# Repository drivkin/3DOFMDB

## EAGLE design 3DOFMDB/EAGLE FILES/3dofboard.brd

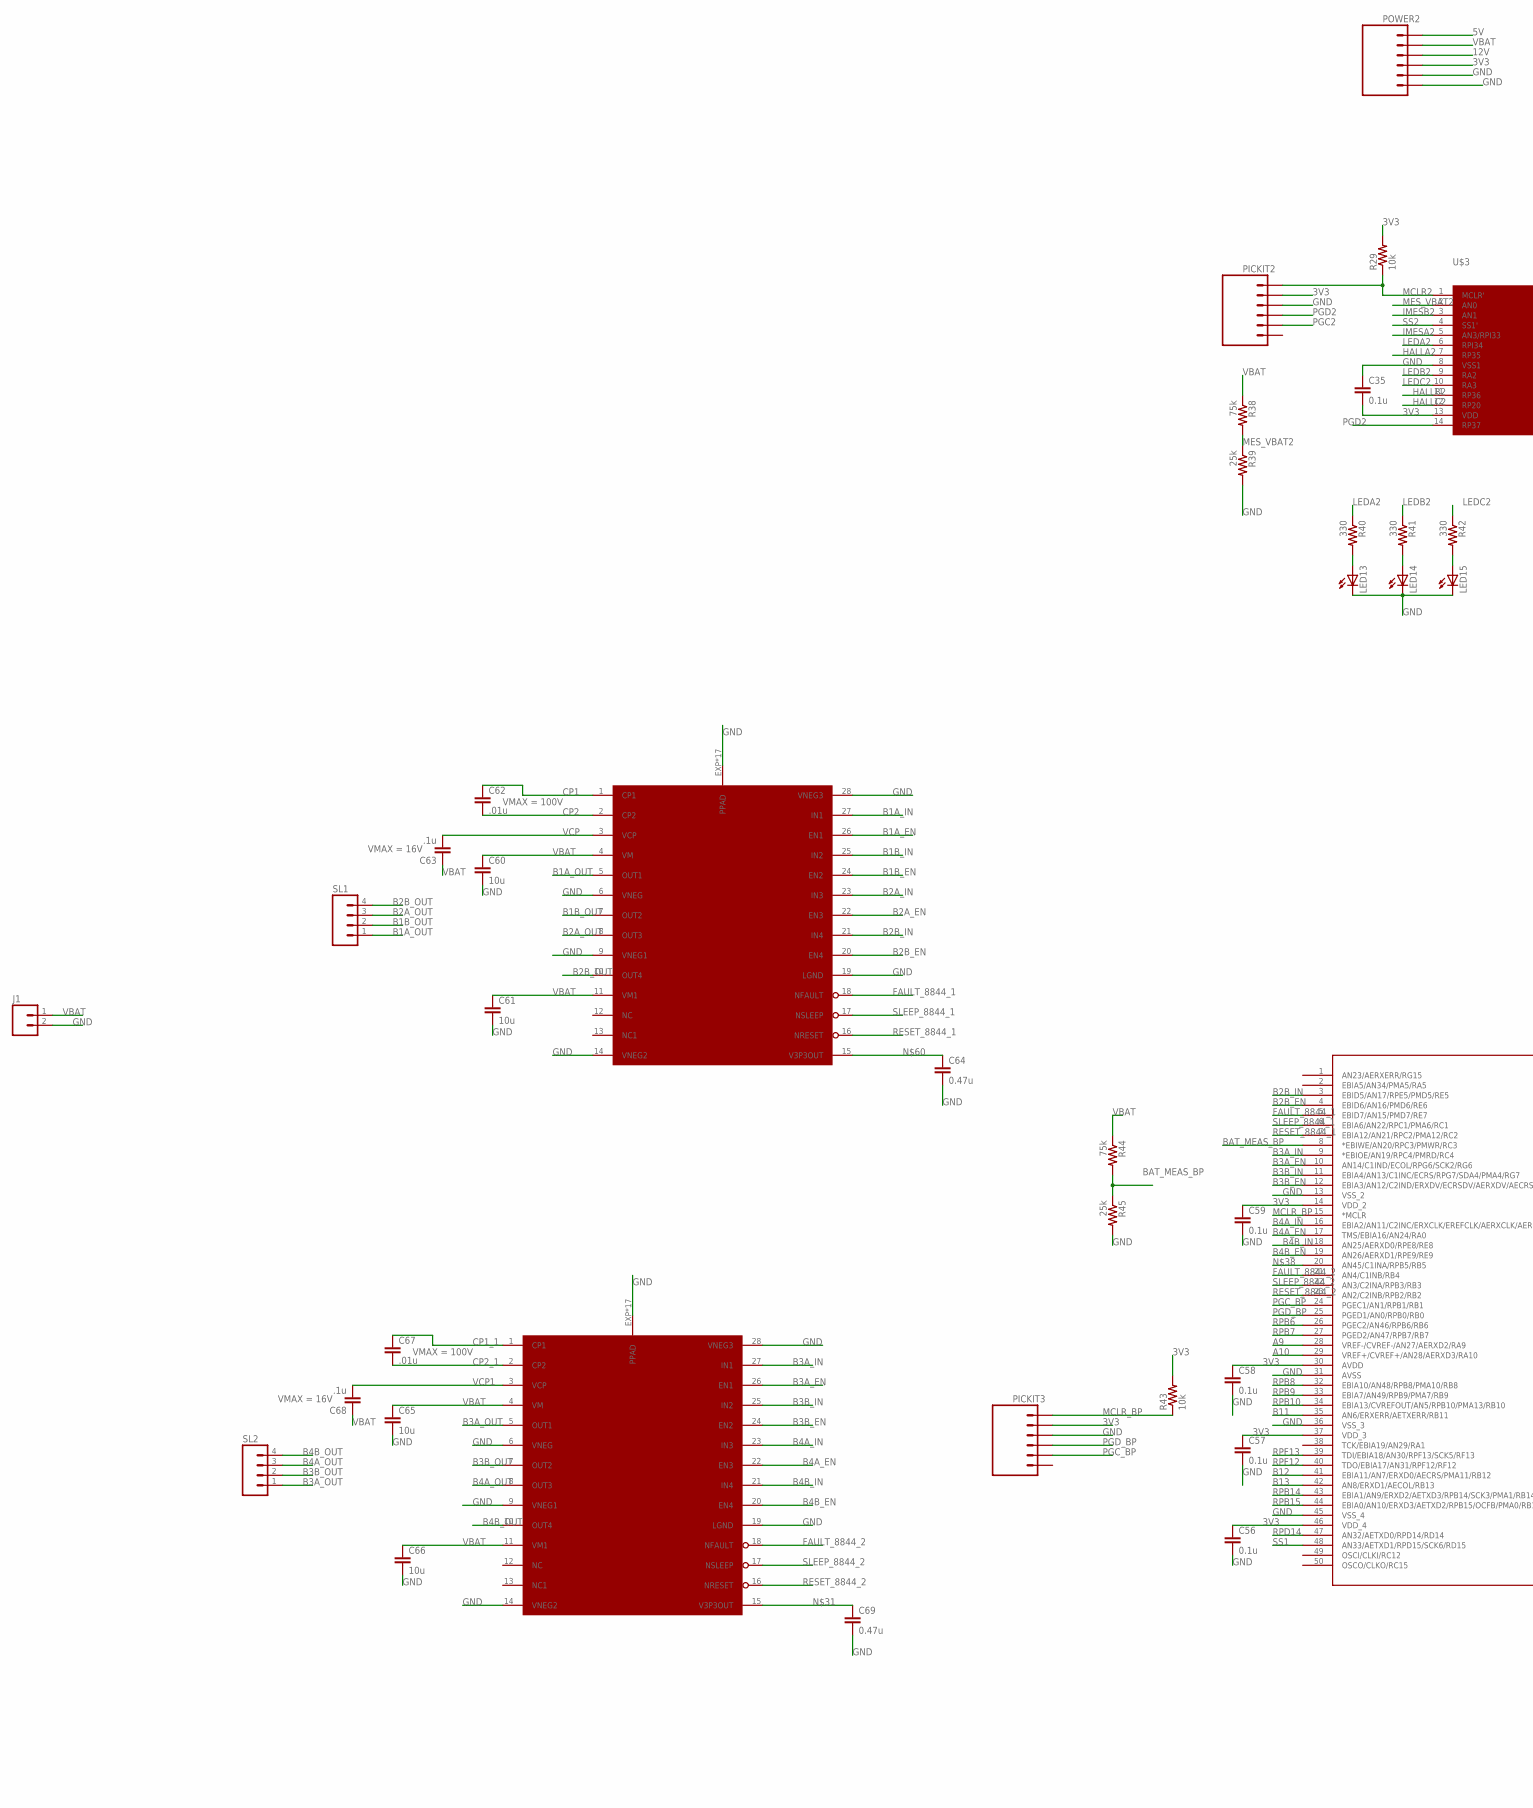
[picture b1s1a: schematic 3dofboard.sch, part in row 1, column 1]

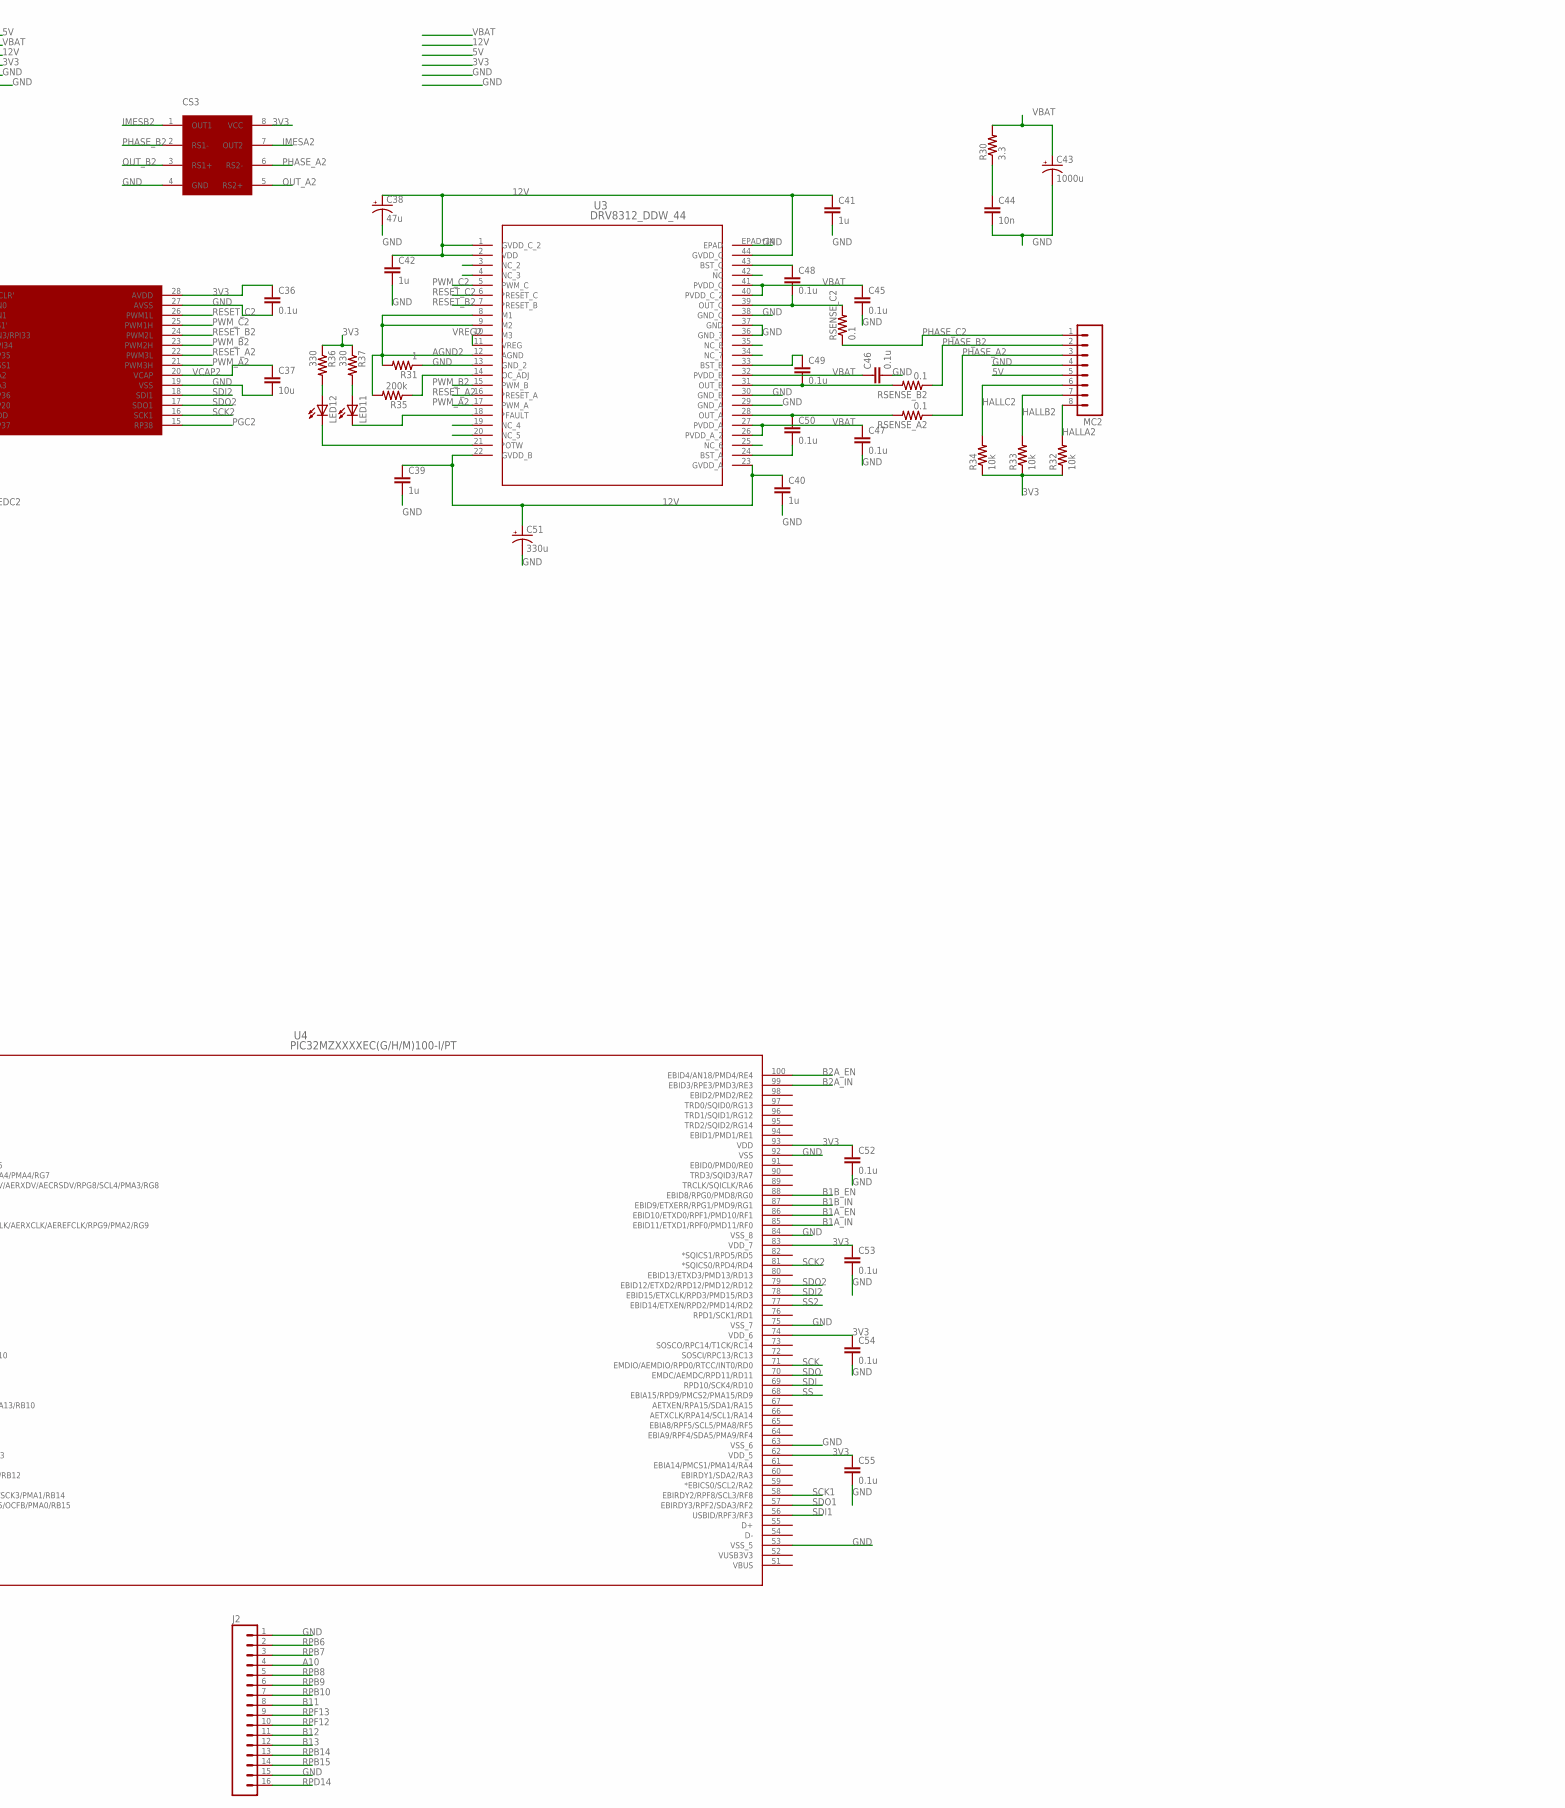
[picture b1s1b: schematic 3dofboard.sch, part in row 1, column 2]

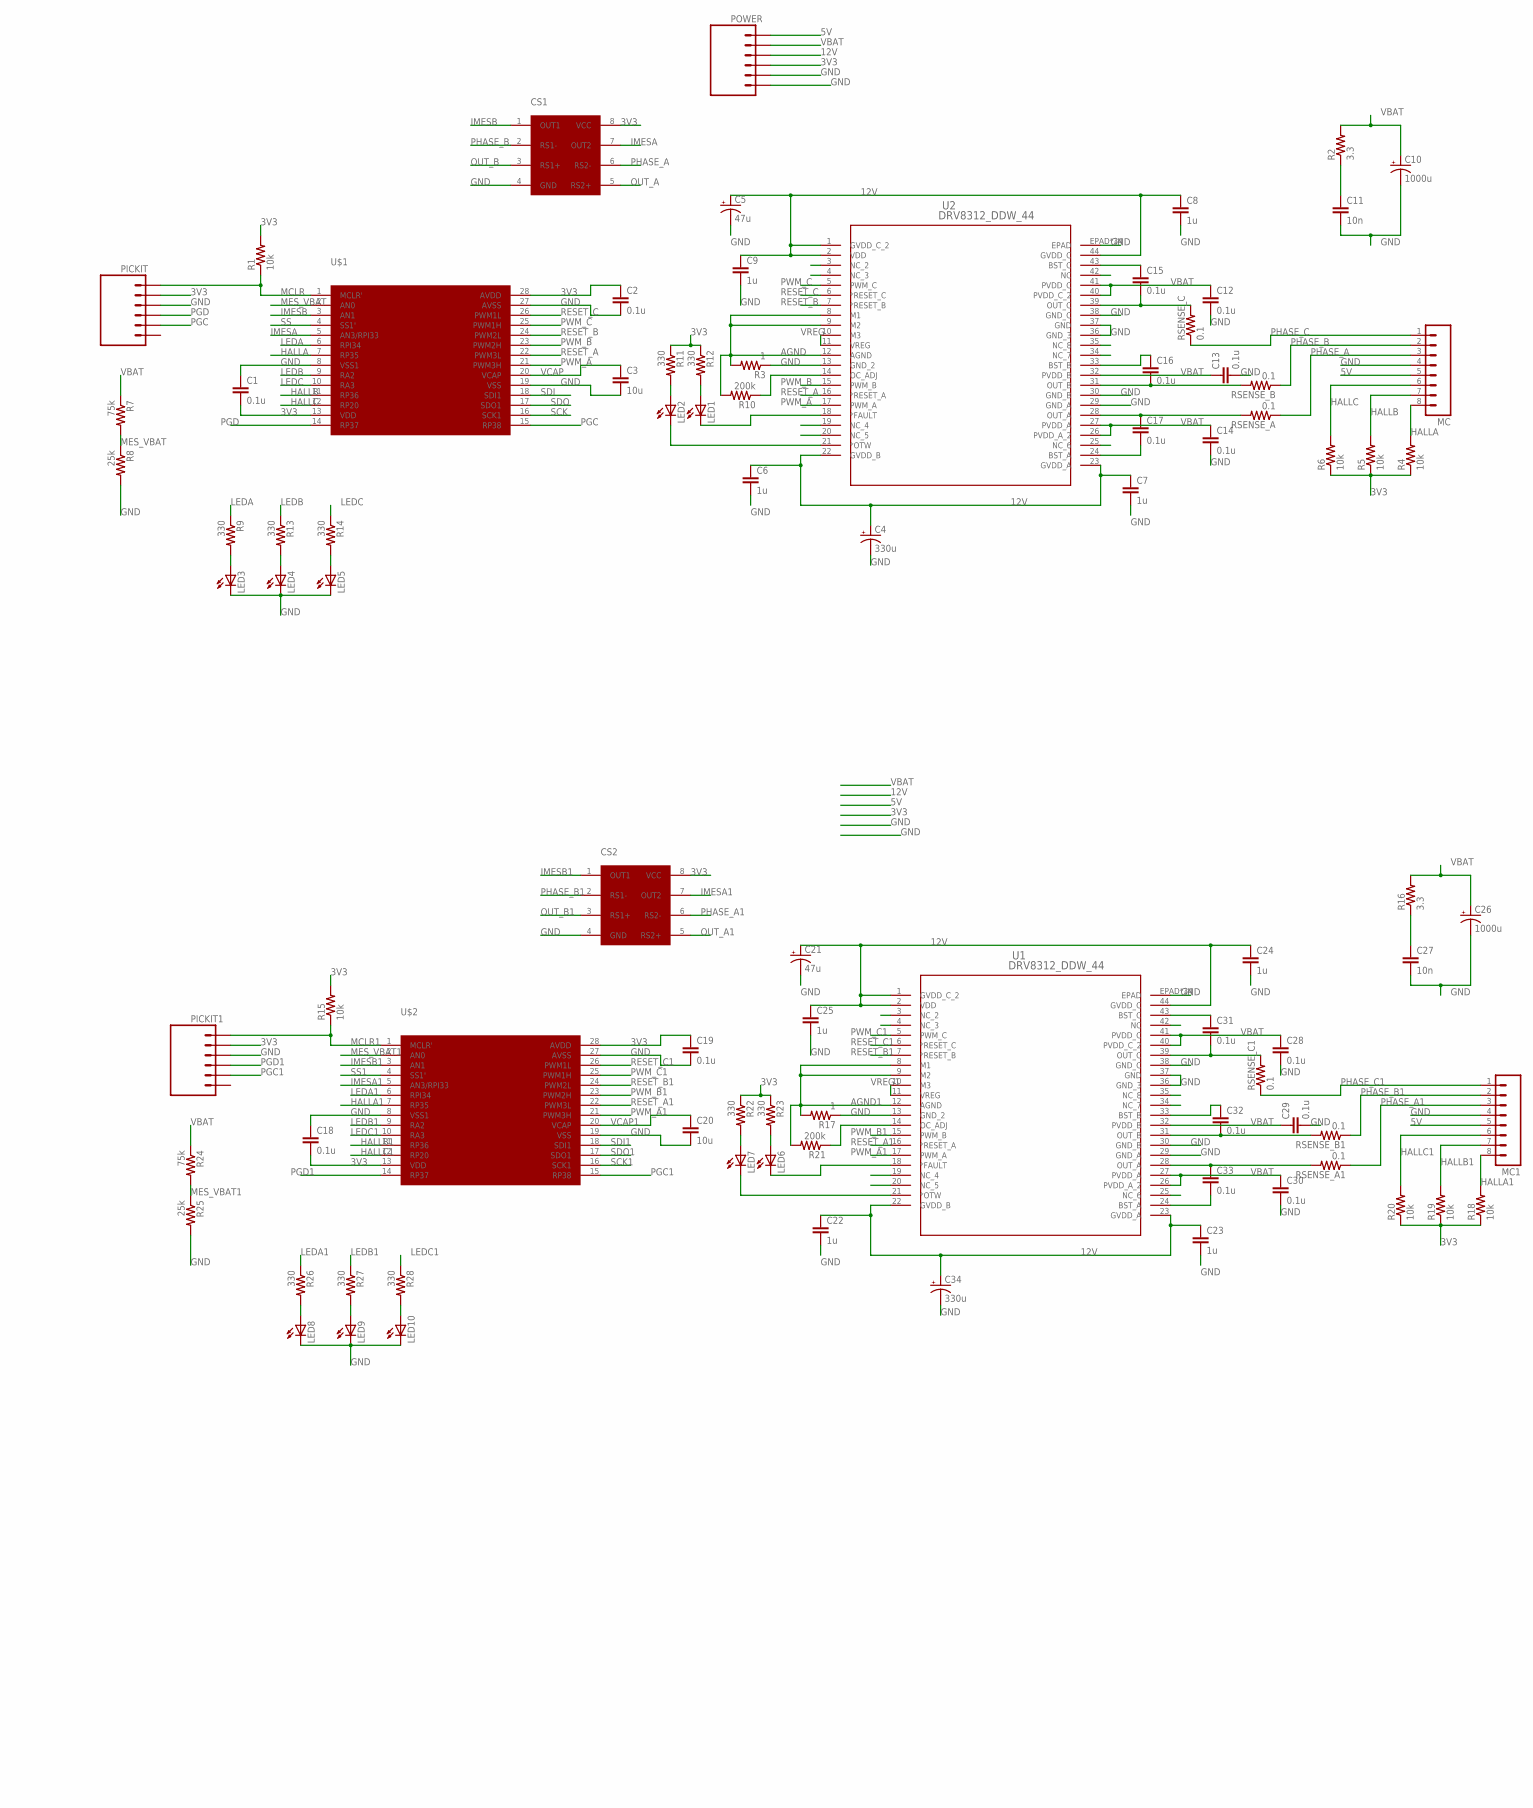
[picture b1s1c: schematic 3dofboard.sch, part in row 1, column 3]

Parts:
C1, C2, C12, C13, C14, C15, C16, C17, C18, C19, C28, C29, C30, C31, C32, C33, C35, C36, C45, C46, C47, C48, C49, C50, C52, C53, C54, C55, C56, C57, C58, C59: 0.1u; 0805
C3, C20, C37, C60, C61, C65, C66: 10u; 0805
C4, C34, C51: 330u; E3,5-8
C5, C21, C38: 47u; CPOL-RADIAL-100UF-25V
C6, C7, C8, C9, C22, C23, C24, C25, C39, C40, C41, C42: 1u; 0805
C10, C26, C43: 1000u; CPOL-RADIAL-1000UF-25V
C11, C27, C44: 10n; 0805
C62, C67: .01u; 0805
C63, C68: .1u; 0805
C64, C69: 0.47u; 0805
CS1, CS2, CS3: MAX4376; SO8
J1: M02LOCK; 1X02_LOCK
J2: M16DUAL_ROW; 2X8
LED1, LED2, LED3, LED4, LED5, LED6, LED7, LED8, LED9, LED10, LED11, LED12, LED13, LED14, LED15: LED0805; LED-0805
MC, MC1, MC2: M08; 08P
PICKIT, PICKIT1, PICKIT2, PICKIT3: M06LOCK; 1X06_LOCK
POWER, POWER2: M06LOCK; 1X06_LOCK
R1, R4, R5, R6, R15, R18, R19, R20, R29, R32, R33, R34, R43: 10k; 0805
R2, R16, R30: 3.3; 0805
R3, R17, R31: 1; 0805
R7, R24, R38, R44: 75k; 0805
R8, R25, R39, R45: 25k; 0805
R9, R11, R12, R13, R14, R22, R23, R26, R27, R28, R36, R37, R40, R41, R42: 330; 0805
R10, R21, R35: 200k; 0805
RSENSE_A, RSENSE_A1, RSENSE_A2: 0.1; 0805
RSENSE_B, RSENSE_B1, RSENSE_B2: 0.1; 0805
RSENSE_C, RSENSE_C1, RSENSE_C2: 0.1; 0805
SL1, SL2: M04LOCK; 1X04_LOCK
U1, U2, U3: DRV8312_DDW_44; DDW44_8P26X4P31
U4: PIC32MZXXXXEC(G/H/M)100-I/PT; TQFP100_12X12MC
U$1, U$2, U$3: DSPIC33EP512MC502-28SSOP; SSOP28
U$4, U$5: DRV8844PWP; TSSOP-28

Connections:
3V3: C1.2, C2.1, C18.2, C19.1, C35.2, C36.1, C52.1, C53.1, C54.1, C55.1, C56.1, C57.1, C58.1, C59.1, CS1.8 (VCC), CS2.8 (VCC), CS3.8 (VCC), PICKIT.2, PICKIT1.2, PICKIT2.2, PICKIT3.2, POWER.4, POWER2.4, R1.2, R4.1, R5.1, R6.1, R11.1, R12.1, R15.2, R18.1, R19.1, R20.1, R22.1, R23.1, R29.2, R32.1, R33.1, R34.1, R36.1, R37.1, R43.2, U4.14 (VDD_2), U4.30 (AVDD), U4.37 (VDD_3), U4.46 (VDD_4), U4.62 (VDD_5), U4.74 (VDD_6), U4.83 (VDD_7), U4.93 (VDD), U$1.13 (VDD), U$1.28 (AVDD), U$2.13 (VDD), U$2.28 (AVDD), U$3.13 (VDD), U$3.28 (AVDD)
5V: MC.5, MC1.5, MC2.5, POWER.1, POWER2.1
12V: C4.+, C5.1 (+), C6.1, C7.1, C8.1, C9.1, C21.1 (+), C22.1, C23.1, C24.1, C25.1, C34.+, C38.1 (+), C39.1, C40.1, C41.1, C42.1, C51.+, POWER.3, POWER2.3, U1.1 (GVDD_C_2), U1.2 (VDD), U1.22 (GVDD_B), U1.23 (GVDD_A), U1.44 (GVDD_C), U2.1 (GVDD_C_2), U2.2 (VDD), U2.22 (GVDD_B), U2.23 (GVDD_A), U2.44 (GVDD_C), U3.1 (GVDD_C_2), U3.2 (VDD), U3.22 (GVDD_B), U3.23 (GVDD_A), U3.44 (GVDD_C)
A9: U4.28 (VREF-/CVREF-/AN27/AERXD2/RA9)
A10: J2.4, U4.29 (VREF+/CVREF+/AN28/AERXD3/RA10)
AGND: R3.2, R10.2, U2.8 (M1), U2.9 (M2), U2.12 (AGND)
AGND1: R17.2, R21.2, U1.8 (M1), U1.9 (M2), U1.12 (AGND)
AGND2: R31.2, R35.2, U3.8 (M1), U3.9 (M2), U3.12 (AGND)
B1A_EN: U4.86 (EBID10/ETXD0/RPF1/PMD10/RF1), U$4.26 (EN1)
B1A_IN: U4.85 (EBID11/ETXD1/RPF0/PMD11/RF0), U$4.27 (IN1)
B1A_OUT: SL1.1, U$4.5 (OUT1)
B1B_EN: U4.88 (EBID8/RPG0/PMD8/RG0), U$4.24 (EN2)
B1B_IN: U4.87 (EBID9/ETXERR/RPG1/PMD9/RG1), U$4.25 (IN2)
B1B_OUT: SL1.2, U$4.7 (OUT2)
B2A_EN: U4.100 (EBID4/AN18/PMD4/RE4), U$4.22 (EN3)
B2A_IN: U4.99 (EBID3/RPE3/PMD3/RE3), U$4.23 (IN3)
B2A_OUT: SL1.3, U$4.8 (OUT3)
B2B_EN: U4.4 (EBID6/AN16/PMD6/RE6), U$4.20 (EN4)
B2B_IN: U4.3 (EBID5/AN17/RPE5/PMD5/RE5), U$4.21 (IN4)
B2B_OUT: SL1.4, U$4.10 (OUT4)
B3A_EN: U4.10 (AN14/C1IND/ECOL/RPG6/SCK2/RG6), U$5.26 (EN1)
B3A_IN: U4.9 (*EBIOE/AN19/RPC4/PMRD/RC4), U$5.27 (IN1)
B3A_OUT: SL2.1, U$5.5 (OUT1)
B3B_EN: U4.12 (EBIA3/AN12/C2IND/ERXDV/ECRSDV/AERXDV/AE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), U$5.24 (EN2)
B3B_IN: U4.11 (EBIA4/AN13/C1INC/ECRS/RPG7/SDA4/PMA4/RG7), U$5.25 (IN2)
B3B_OUT: SL2.2, U$5.7 (OUT2)
B4A_EN: U4.17 (TMS/EBIA16/AN24/RA0), U$5.22 (EN3)
B4A_IN: U4.16 (EBIA2/AN11/C2INC/ERXCLK/EREFCLK/AERXCLK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), U$5.23 (IN3)
B4A_OUT: SL2.3, U$5.8 (OUT3)
B4B_EN: U4.19 (AN26/AERXD1/RPE9/RE9), U$5.20 (EN4)
B4B_IN: U4.18 (AN25/AERXD0/RPE8/RE8), U$5.21 (IN4)
B4B_OUT: SL2.4, U$5.10 (OUT4)
B11: J2.8, U4.35 (AN6/ERXERR/AETXERR/RB11)
B12: J2.11, U4.41 (EBIA11/AN7/ERXD0/AECRS/PMA11/RB12)
B13: J2.12, U4.42 (AN8/ERXD1/AECOL/RB13)
BAT_MEAS_BP: R44.2, R45.1, U4.8 (*EBIWE/AN20/RPC3/PMWR/RC3)
CP1: C62.1, U$4.1 (CP1)
CP1_1: C67.1, U$5.1 (CP1)
CP2: C62.2, U$4.2 (CP2)
CP2_1: C67.2, U$5.2 (CP2)
FAULT': LED1.2 (C), U2.18 (*FAULT)
FAULT'1: LED6.2 (C), U1.18 (*FAULT)
FAULT'2: LED11.2 (C), U3.18 (*FAULT)
FAULT_8844_1: U4.5 (EBID7/AN15/PMD7/RE7), U$4.18 (NFAULT)
FAULT_8844_2: U4.21 (AN4/C1INB/RB4), U$5.18 (NFAULT)
GND: C1.1, C2.2, C3.2, C4.-, C5.2 (-), C6.2, C7.2, C8.2, C9.2, C10.2 (-), C11.2, C12.2, C13.2, C14.2, C18.1, C19.2, C20.2, C21.2 (-), C22.2, C23.2, C24.2, C25.2, C26.2 (-), C27.2, C28.2, C29.2, C30.2, C34.-, C35.1, C36.2, C37.2, C38.2 (-), C39.2, C40.2, C41.2, C42.2, C43.2 (-), C44.2, C45.2, C46.2, C47.2, C51.-, C52.2, C53.2, C54.2, C55.2, C56.2, C57.2, C58.2, C59.2, C60.2, C61.2, C64.2, C65.2, C66.2, C69.2, CS1.4 (GND), CS2.4 (GND), CS3.4 (GND), J1.2 (1), J2.1, J2.15, LED3.2 (C), LED4.2 (C), LED5.2 (C), LED8.2 (C), LED9.2 (C), LED10.2 (C), LED13.2 (C), LED14.2 (C), LED15.2 (C), MC.4, MC1.4, MC2.4, PICKIT.3, PICKIT1.3, PICKIT2.3, PICKIT3.3, POWER.5, POWER.6, POWER2.5, POWER2.6, R3.1, R8.2, R17.1, R25.2, R31.1, R39.2, R45.2, U1.3 (NC_2), U1.4 (NC_3), U1.13 (GND_2), U1.19 (NC_4), U1.20 (NC_5), U1.25 (NC_6), U1.29 (GND_A), U1.30 (GND_B), U1.34 (NC_7), U1.35 (NC_8), U1.36 (GND_3), U1.37 (GND), U1.38 (GND_C), U1.42 (NC), U1.EPAD, U1.P$1 (EPAD), U1.P$2 (EPAD), U1.P$3 (EPAD), U1.P$4 (EPAD), U1.P$5 (EPAD), U1.P$6 (EPAD), U1.P$7 (EPAD), U1.P$8 (EPAD), U1.P$9 (EPAD), U1.P$10 (EPAD), U1.P$11 (EPAD), U1.P$12 (EPAD), U1.P$13 (EPAD), U1.P$14 (EPAD), U1.P$15 (EPAD), U1.P$16 (EPAD), U1.P$17 (EPAD), U1.P$18 (EPAD), U1.P$19 (EPAD), U1.P$20 (EPAD), U1.P$21 (EPAD), U1.P$22 (EPAD), U1.P$23 (EPAD), U1.P$24 (EPAD), U1.P$25 (EPAD), U1.P$26 (EPAD), U1.P$27 (EPAD), U1.P$28 (EPAD), U1.P$29 (EPAD), U1.P$30 (EPAD), U1.P$31 (EPAD), U1.P$32 (EPAD), U1.P$33 (EPAD), U2.3 (NC_2), U2.4 (NC_3), U2.13 (GND_2), U2.19 (NC_4), U2.20 (NC_5), U2.25 (NC_6), U2.29 (GND_A), U2.30 (GND_B), U2.34 (NC_7), U2.35 (NC_8), U2.36 (GND_3), U2.37 (GND), U2.38 (GND_C), U2.42 (NC), U2.EPAD, U2.P$1 (EPAD), U2.P$2 (EPAD), U2.P$3 (EPAD), U2.P$4 (EPAD), U2.P$5 (EPAD), U2.P$6 (EPAD), U2.P$7 (EPAD), U2.P$8 (EPAD), U2.P$9 (EPAD), U2.P$10 (EPAD), U2.P$11 (EPAD), U2.P$12 (EPAD), U2.P$13 (EPAD), U2.P$14 (EPAD), U2.P$15 (EPAD), U2.P$16 (EPAD), U2.P$17 (EPAD), U2.P$18 (EPAD), U2.P$19 (EPAD), U2.P$20 (EPAD), U2.P$21 (EPAD), U2.P$22 (EPAD), U2.P$23 (EPAD), U2.P$24 (EPAD), U2.P$25 (EPAD), U2.P$26 (EPAD), U2.P$27 (EPAD), U2.P$28 (EPAD), U2.P$29 (EPAD), U2.P$30 (EPAD), U2.P$31 (EPAD), U2.P$32 (EPAD), U2.P$33 (EPAD), U3.3 (NC_2), U3.4 (NC_3), U3.13 (GND_2), U3.19 (NC_4), U3.20 (NC_5), U3.25 (NC_6), U3.29 (GND_A), U3.30 (GND_B), U3.34 (NC_7), U3.35 (NC_8), U3.36 (GND_3), U3.37 (GND), U3.38 (GND_C), U3.42 (NC), U3.EPAD, U3.P$1 (EPAD), U3.P$2 (EPAD), U3.P$3 (EPAD), U3.P$4 (EPAD), U3.P$5 (EPAD), U3.P$6 (EPAD), U3.P$7 (EPAD), U3.P$8 (EPAD), U3.P$9 (EPAD), U3.P$10 (EPAD), U3.P$11 (EPAD), U3.P$12 (EPAD), U3.P$13 (EPAD), U3.P$14 (EPAD), U3.P$15 (EPAD), U3.P$16 (EPAD), U3.P$17 (EPAD), U3.P$18 (EPAD), U3.P$19 (EPAD), U3.P$20 (EPAD), U3.P$21 (EPAD), U3.P$22 (EPAD), U3.P$23 (EPAD), U3.P$24 (EPAD), U3.P$25 (EPAD), U3.P$26 (EPAD), U3.P$27 (EPAD), U3.P$28 (EPAD), U3.P$29 (EPAD), U3.P$30 (EPAD), U3.P$31 (EPAD), U3.P$32 (EPAD), U3.P$33 (EPAD), U4.13 (VSS_2), U4.31 (AVSS), U4.36 (VSS_3), U4.45 (VSS_4), U4.53 (VSS_5), U4.63 (VSS_6), U4.75 (VSS_7), U4.84 (VSS_8), U4.92 (VSS), U$1.8 (VSS1), U$1.19 (VSS), U$1.27 (AVSS), U$2.8 (VSS1), U$2.19 (VSS), U$2.27 (AVSS), U$3.8 (VSS1), U$3.19 (VSS), U$3.27 (AVSS), U$4.6 (VNEG), U$4.9 (VNEG1), U$4.14 (VNEG2), U$4.19 (LGND), U$4.28 (VNEG3), U$4.EXP (PPAD), U$4.P$1 (PPAD), U$4.P$2 (PPAD), U$4.P$3 (PPAD), U$4.P$4 (PPAD), U$4.P$5 (PPAD), U$4.P$6 (PPAD), U$4.P$7 (PPAD), U$4.P$8 (PPAD), U$4.P$9 (PPAD), U$4.P$10 (PPAD), U$4.P$11 (PPAD), U$4.P$12 (PPAD), U$4.P$13 (PPAD), U$4.P$14 (PPAD), U$4.P$15 (PPAD), U$4.P$16 (PPAD), U$5.6 (VNEG), U$5.9 (VNEG1), U$5.14 (VNEG2), U$5.19 (LGND), U$5.28 (VNEG3), U$5.EXP (PPAD), U$5.P$1 (PPAD), U$5.P$2 (PPAD), U$5.P$3 (PPAD), U$5.P$4 (PPAD), U$5.P$5 (PPAD), U$5.P$6 (PPAD), U$5.P$7 (PPAD), U$5.P$8 (PPAD), U$5.P$9 (PPAD), U$5.P$10 (PPAD), U$5.P$11 (PPAD), U$5.P$12 (PPAD), U$5.P$13 (PPAD), U$5.P$14 (PPAD), U$5.P$15 (PPAD), U$5.P$16 (PPAD)
HALLA: MC.8, R4.2, U$1.7 (RP35)
HALLA1: MC1.8, R18.2, U$2.7 (RP35)
HALLA2: MC2.8, R32.2, U$3.7 (RP35)
HALLB: MC.7, R5.2, U$1.11 (RP36)
HALLB1: MC1.7, R19.2, U$2.11 (RP36)
HALLB2: MC2.7, R33.2, U$3.11 (RP36)
HALLC: MC.6, R6.2, U$1.12 (RP20)
HALLC1: MC1.6, R20.2, U$2.12 (RP20)
HALLC2: MC2.6, R34.2, U$3.12 (RP20)
IMESA: CS1.7 (OUT2), U$1.5 (AN3/RPI33)
IMESA1: CS2.7 (OUT2), U$2.5 (AN3/RPI33)
IMESA2: CS3.7 (OUT2), U$3.5 (AN3/RPI33)
IMESB: CS1.1 (OUT1), U$1.3 (AN1)
IMESB1: CS2.1 (OUT1), U$2.3 (AN1)
IMESB2: CS3.1 (OUT1), U$3.3 (AN1)
LEDA: R9.1, U$1.6 (RPI34)
LEDA1: R26.1, U$2.6 (RPI34)
LEDA2: R40.1, U$3.6 (RPI34)
LEDB: R13.1, U$1.9 (RA2)
LEDB1: R27.1, U$2.9 (RA2)
LEDB2: R41.1, U$3.9 (RA2)
LEDC: R14.1, U$1.10 (RA3)
LEDC1: R28.1, U$2.10 (RA3)
LEDC2: R42.1, U$3.10 (RA3)
MCLR: PICKIT.1, R1.1, U$1.1 (MCLR')
MCLR1: PICKIT1.1, R15.1, U$2.1 (MCLR')
MCLR2: PICKIT2.1, R29.1, U$3.1 (MCLR')
MCLR_BP: PICKIT3.1, R43.1, U4.15 (*MCLR)
MES_VBAT: R7.2, R8.1, U$1.2 (AN0)
MES_VBAT1: R24.2, R25.1, U$2.2 (AN0)
MES_VBAT2: R38.2, R39.1, U$3.2 (AN0)
unnamed: C11.1, R2.1
unnamed: LED3.1 (A), R9.2
unnamed: LED4.1 (A), R13.2
unnamed: R10.1, U2.14 (OC_ADJ)
unnamed: C17.2, U2.24 (BST_A)
unnamed: LED1.1 (A), R12.2
unnamed: C16.1, U2.33 (BST_B)
unnamed: C15.1, U2.43 (BST_C)
unnamed: LED2.1 (A), R11.2
unnamed: LED5.1 (A), R14.2
unnamed: C27.1, R16.1
unnamed: C33.2, U1.24 (BST_A)
unnamed: C32.1, U1.33 (BST_B)
unnamed: C31.1, U1.43 (BST_C)
unnamed: R21.1, U1.14 (OC_ADJ)
unnamed: LED6.1 (A), R23.2
unnamed: LED7.1 (A), R22.2
unnamed: LED8.1 (A), R26.2
unnamed: LED9.1 (A), R27.2
unnamed: LED10.1 (A), R28.2
unnamed: C44.1, R30.1
unnamed: C50.2, U3.24 (BST_A)
unnamed: C49.1, U3.33 (BST_B)
unnamed: C48.1, U3.43 (BST_C)
unnamed: R35.1, U3.14 (OC_ADJ)
unnamed: LED11.1 (A), R37.2
unnamed: LED12.1 (A), R36.2
unnamed: LED13.1 (A), R40.2
unnamed: LED14.1 (A), R41.2
unnamed: LED15.1 (A), R42.2
unnamed: C69.1, U$5.15 (V3P3OUT)
unnamed: C64.1, U$4.15 (V3P3OUT)
OTW': LED2.2 (C), U2.21 (*OTW)
OTW'1: LED7.2 (C), U1.21 (*OTW)
OTW'2: LED12.2 (C), U3.21 (*OTW)
OUT_A: C17.1, CS1.5 (RS2+), RSENSE_A.2, U2.28 (OUT_A)
OUT_A1: C33.1, CS2.5 (RS2+), RSENSE_A1.2, U1.28 (OUT_A)
OUT_A2: C50.1, CS3.5 (RS2+), RSENSE_A2.2, U3.28 (OUT_A)
OUT_B: C16.2, CS1.3 (RS1+), RSENSE_B.2, U2.31 (OUT_B)
OUT_B1: C32.2, CS2.3 (RS1+), RSENSE_B1.2, U1.31 (OUT_B)
OUT_B2: C49.2, CS3.3 (RS1+), RSENSE_B2.2, U3.31 (OUT_B)
OUT_C: C15.2, RSENSE_C.2, U2.39 (OUT_C)
OUT_C1: C31.2, RSENSE_C1.2, U1.39 (OUT_C)
OUT_C2: C48.2, RSENSE_C2.2, U3.39 (OUT_C)
PGC: PICKIT.5, U$1.15 (RP38)
PGC1: PICKIT1.5, U$2.15 (RP38)
PGC2: PICKIT2.5, U$3.15 (RP38)
PGC_BP: PICKIT3.5, U4.24 (PGEC1/AN1/RPB1/RB1)
PGD: PICKIT.4, U$1.14 (RP37)
PGD1: PICKIT1.4, U$2.14 (RP37)
PGD2: PICKIT2.4, U$3.14 (RP37)
PGD_BP: PICKIT3.4, U4.25 (PGED1/AN0/RPB0/RB0)
PHASE_A: CS1.6 (RS2-), MC.3, RSENSE_A.1
PHASE_A1: CS2.6 (RS2-), MC1.3, RSENSE_A1.1
PHASE_A2: CS3.6 (RS2-), MC2.3, RSENSE_A2.1
PHASE_B: CS1.2 (RS1-), MC.2, RSENSE_B.1
PHASE_B1: CS2.2 (RS1-), MC1.2, RSENSE_B1.1
PHASE_B2: CS3.2 (RS1-), MC2.2, RSENSE_B2.1
PHASE_C: MC.1, RSENSE_C.1
PHASE_C1: MC1.1, RSENSE_C1.1
PHASE_C2: MC2.1, RSENSE_C2.1
PWM_A: U2.17 (PWM_A), U$1.21 (PWM3H)
PWM_A1: U1.17 (PWM_A), U$2.21 (PWM3H)
PWM_A2: U3.17 (PWM_A), U$3.21 (PWM3H)
PWM_B: U2.15 (PWM_B), U$1.23 (PWM2H)
PWM_B1: U1.15 (PWM_B), U$2.23 (PWM2H)
PWM_B2: U3.15 (PWM_B), U$3.23 (PWM2H)
PWM_C: U2.5 (PWM_C), U$1.25 (PWM1H)
PWM_C1: U1.5 (PWM_C), U$2.25 (PWM1H)
PWM_C2: U3.5 (PWM_C), U$3.25 (PWM1H)
RESET_8844_1: U4.7 (EBIA12/AN21/RPC2/PMA12/RC2), U$4.16 (NRESET)
RESET_8844_2: U4.23 (AN2/C2INB/RPB2/RB2), U$5.16 (NRESET)
RESET_A: U2.16 (*RESET_A), U$1.22 (PWM3L)
RESET_A1: U1.16 (*RESET_A), U$2.22 (PWM3L)
RESET_A2: U3.16 (*RESET_A), U$3.22 (PWM3L)
RESET_B: U2.7 (*RESET_B), U$1.24 (PWM2L)
RESET_B1: U1.7 (*RESET_B), U$2.24 (PWM2L)
RESET_B2: U3.7 (*RESET_B), U$3.24 (PWM2L)
RESET_C: U2.6 (*RESET_C), U$1.26 (PWM1L)
RESET_C1: U1.6 (*RESET_C), U$2.26 (PWM1L)
RESET_C2: U3.6 (*RESET_C), U$3.26 (PWM1L)
RPB6: J2.2, U4.26 (PGEC2/AN46/RPB6/RB6)
RPB7: J2.3, U4.27 (PGED2/AN47/RPB7/RB7)
RPB8: J2.5, U4.32 (EBIA10/AN48/RPB8/PMA10/RB8)
RPB9: J2.6, U4.33 (EBIA7/AN49/RPB9/PMA7/RB9)
RPB10: J2.7, U4.34 (EBIA13/CVREFOUT/AN5/RPB10/PMA13/RB10)
RPB14: J2.13, U4.43 (EBIA1/AN9/ERXD2/AETXD3/RPB14/SCK3/PMA1/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)
RPB15: J2.14, U4.44 (EBIA0/AN10/ERXD3/AETXD2/RPB15/OCFB/PMA0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)
RPD14: J2.16, U4.47 (AN32/AETXD0/RPD14/RD14)
RPF12: J2.10, U4.40 (TDO/EBIA17/AN31/RPF12/RF12)
RPF13: J2.9, U4.39 (TDI/EBIA18/AN30/RPF13/SCK5/RF13)
SCK: U4.71 (EMDIO/AEMDIO/RPD0/RTCC/INT0/RD0), U$1.16 (SCK1)
SCK1: U4.58 (EBIRDY2/RPF8/SCL3/RF8), U$2.16 (SCK1)
SCK2: U4.81 (*SQICS0/RPD4/RD4), U$3.16 (SCK1)
SDI: U4.69 (RPD10/SCK4/RD10), U$1.18 (SDI1)
SDI1: U4.56 (USBID/RPF3/RF3), U$2.18 (SDI1)
SDI2: U4.78 (EBID15/ETXCLK/RPD3/PMD15/RD3), U$3.18 (SDI1)
SDO: U4.70 (EMDC/AEMDC/RPD11/RD11), U$1.17 (SDO1)
SDO1: U4.57 (EBIRDY3/RPF2/SDA3/RF2), U$2.17 (SDO1)
SDO2: U4.79 (EBID12/ETXD2/RPD12/PMD12/RD12), U$3.17 (SDO1)
SLEEP_8844_1: U4.6 (EBIA6/AN22/RPC1/PMA6/RC1), U$4.17 (NSLEEP)
SLEEP_8844_2: U4.22 (AN3/C2INA/RPB3/RB3), U$5.17 (NSLEEP)
SS: U4.68 (EBIA15/RPD9/PMCS2/PMA15/RD9), U$1.4 (SS1')
SS1: U4.48 (AN33/AETXD1/RPD15/SCK6/RD15), U$2.4 (SS1')
SS2: U4.77 (EBID14/ETXEN/RPD2/PMD14/RD2), U$3.4 (SS1')
VBAT: C10.1 (+), C12.1, C13.1, C14.1, C26.1 (+), C28.1, C29.1, C30.1, C43.1 (+), C45.1, C46.1, C47.1, C60.1, C61.1, C63.1, C65.1, C66.1, C68.1, J1.1 (2), POWER.2, POWER2.2, R2.2, R7.1, R16.2, R24.1, R30.2, R38.1, R44.1, U1.26 (PVDD_A_2), U1.27 (PVDD_A), U1.32 (PVDD_B), U1.40 (PVDD_C_2), U1.41 (PVDD_C), U2.26 (PVDD_A_2), U2.27 (PVDD_A), U2.32 (PVDD_B), U2.40 (PVDD_C_2), U2.41 (PVDD_C), U3.26 (PVDD_A_2), U3.27 (PVDD_A), U3.32 (PVDD_B), U3.40 (PVDD_C_2), U3.41 (PVDD_C), U$4.4 (VM), U$4.11 (VM1), U$5.4 (VM), U$5.11 (VM1)
VBUS: U4.51 (VBUS)
VCAP: C3.1, U$1.20 (VCAP)
VCAP1: C20.1, U$2.20 (VCAP)
VCAP2: C37.1, U$3.20 (VCAP)
VCP: C63.2, U$4.3 (VCP)
VCP1: C68.2, U$5.3 (VCP)
VREG: U2.10 (M3), U2.11 (VREG)
VREG1: U1.10 (M3), U1.11 (VREG)
VREG2: U3.10 (M3), U3.11 (VREG)
VUSB3V3: U4.52 (VUSB3V3)

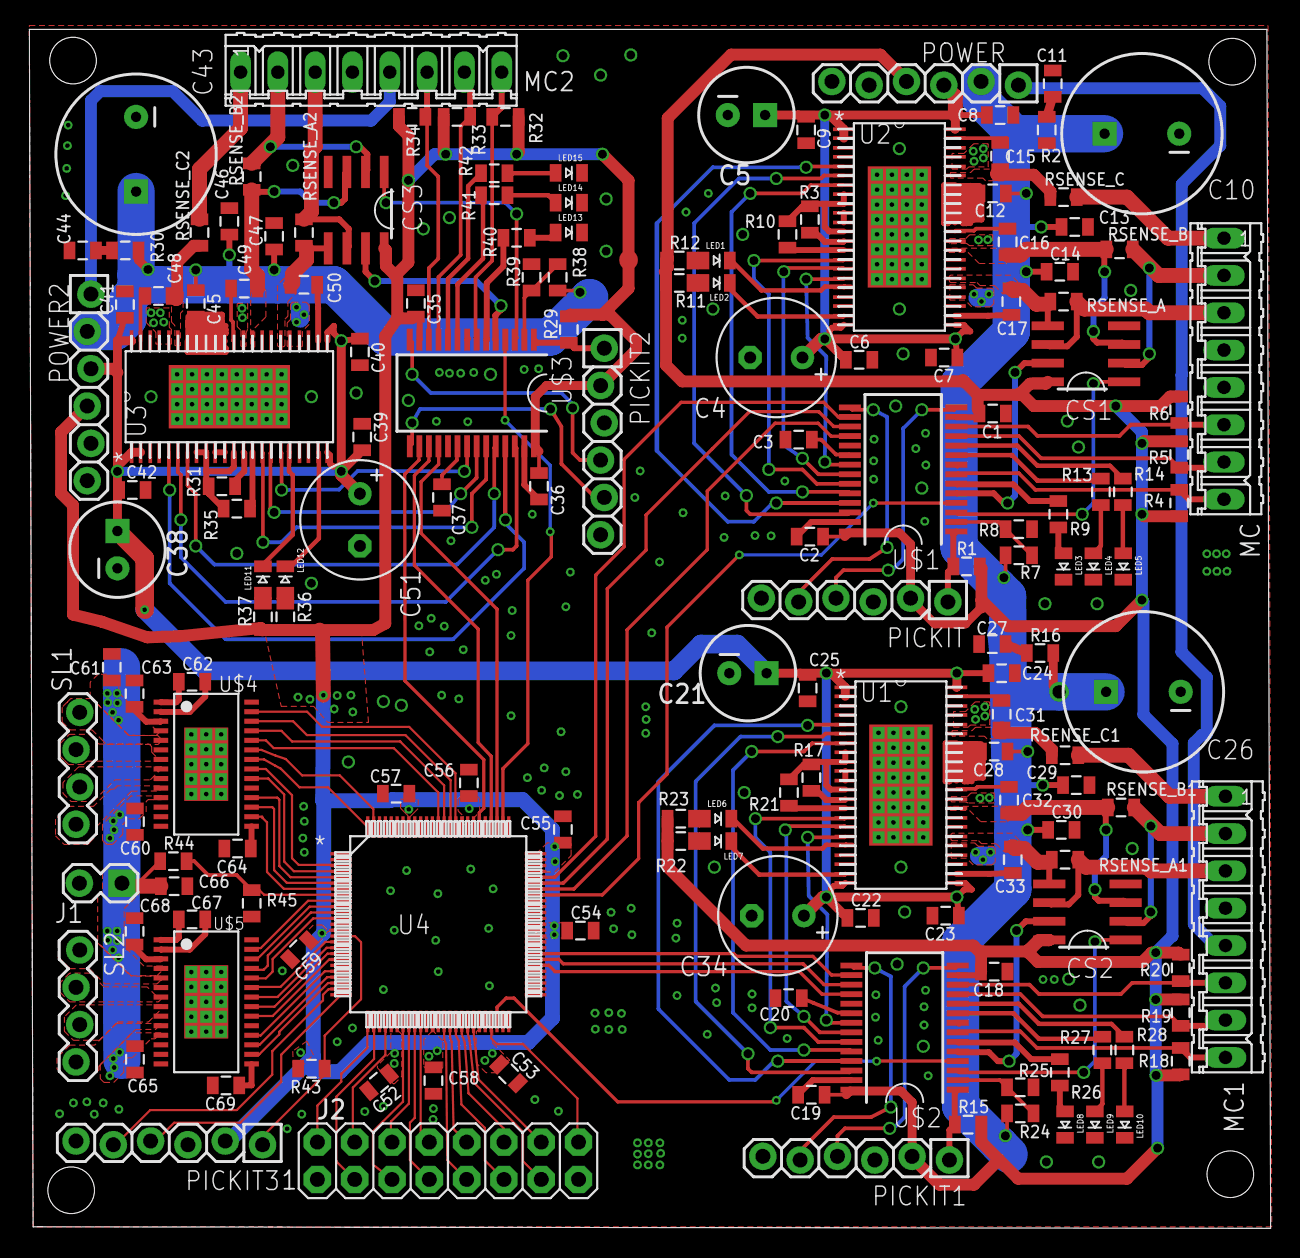
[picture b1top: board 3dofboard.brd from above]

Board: 2 copper layers, 84.5 x 81.6 mm, 163 parts (0 on the bottom side), 190 nets.

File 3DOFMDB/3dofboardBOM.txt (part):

Partlist exported from C:/Users/Dmitriy/Documents/GitHub/3DOFMDB/3DOFMDB/EAGLE FILES/3dofboard.sch at 4/8/2015 4:04:12 PM

Qty Value                        Device                       Package                Parts                                                                                                                                                        Description                          DATASHEETURL                      DESCRIPTION                                                                   DSPIC33EP512MC502 FAMILY_NAME              GENERIC_PART_NUMBER INDUSTRY_STD_PKG_TYPE MANUFACTURER      MANUFACTURER_PART_NUMBER MF MPN OC_FARNELL OC_NEWARK PACKAGE_DESIGNATOR PIN_COUNT VENDOR            VMAX
3                                DSPIC33EP512MC502-28SSOP     SSOP28                 U$1, U$2, U$3                                                                                                                                                DSPIC33EP512MC502                                                                                                                                                                                                                                                                                                                                                   
15                               LED0805                      LED-0805               LED1, LED2, LED3, LED4, LED5, LED6, LED7, LED8, LED9, LED10, LED11, LED12, LED13, LED14, LED15                                                               LEDs                                                                                                                                                                                                                                                                                                                                                                
1                                M02LOCK                      1X02_LOCK              J1                                                                                                                                                           Header 2                                                                                                                                                                                                                                                                                                                                                            
2                                M04LOCK                      1X04_LOCK              SL1, SL2                                                                                                                                                     AMP QUICK CONNECTOR                                                                                                                                                                                                                                                                                                                                                 
6                                M06LOCK                      1X06_LOCK              PICKIT, PICKIT1, PICKIT2, PICKIT3, POWER, POWER2                                                                                                             Header 6                                                                                                                                                                                                                                                                                                                                                            
3                                M08                          08P                    MOTOR_CONNECT, MOTOR_CONNECT1, MOTOR_CONNECT2                                                                                                                AMP QUICK CONNECTOR                                                                                                                                                                                                                                                                         unknown    unknown                                                      
2   .01u                         CAP0805                      0805                   C62, C67                                                                                                                                                     Capacitor                                                                                                                                                                                                                                                                                                                                                       100V
2   .1u                          CAP0805                      0805                   C63, C68                                                                                                                                                     Capacitor                                                                                                                                                                                                                                                                                                                                                       16V 
9   0.1                          RESISTOR0805-RES             0805                   RSENSE_A, RSENSE_A1, RSENSE_A2, RSENSE_B, RSENSE_B1, RSENSE_B2, RSENSE_C, RSENSE_C1, RSENSE_C2                                                               Resistor                                                                                                                                                                                                                                                                                                                                                            
32  0.1u                         CAP0805                      0805                   C1, C2, C12, C13, C14, C15, C16, C17, C18, C19, C28, C29, C30, C31, C32, C33, C35, C36, C45, C46, C47, C48, C49, C50, C52, C53, C54, C55, C56, C57, C58, C59 Capacitor                                                                                                                                                                                                                                                                                                                                                           
2   0.47u                        CAP0805                      0805                   C64, C69                                                                                                                                                     Capacitor                                                                                                                                                                                                                                                                                                                                                           
3   1                            RESISTOR0805-RES             0805                   R3, R17, R31                                                                                                                                                 Resistor                                                                                                                                                                                                                                                                                                                                                            
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
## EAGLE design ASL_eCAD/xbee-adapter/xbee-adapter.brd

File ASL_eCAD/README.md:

# ASL_eCAD

## Description

This repository contains all of the general-purpose electrical CAD projects produced & used by the Autonomous Systems Lab at UCSC under the direction of Professor Gabriel Elkaim. Descriptions of each project are in their respective folders. In the root folder you will find the Eagle 5.11 library used by all of these projects.

## CAD Standards

The following are accepted standards for the circuits that we use:
 * Standard sizes:
   * SMD resistors should be 0805
   * SMD capacitors should be 1206
   * SMD LEDs should be 1206. We stock amber, green, and red.
 * For connectors:
   * For power use the POW_CONNECT part. There are vertical and right-angle connectors. V_in is always pin 1.
   * For general-use headers, we have 2x7 female .1" spaced headers.
   * For single-row .1" headers use the staggered pins. With plated vias these allow for no-solder connections and also make soldering them in easier.
   * If screw terminals are needed, we stock the 5.08mm ones.
 * Trace widths:
   * For standard traces use 16mil.
   * For power traces use 30mil as a minimum for power-carrying traces. There are online trace width calculators available to determine appropriate sizes for high-current applications.
   * For traces that connect through .1" double-row headers use 10mil to pass DRC.
 * General:
   * Use a ground-plane wherever possible.
   * Place all SMD components on one side so that skilleting or using a reflow oven is possible.

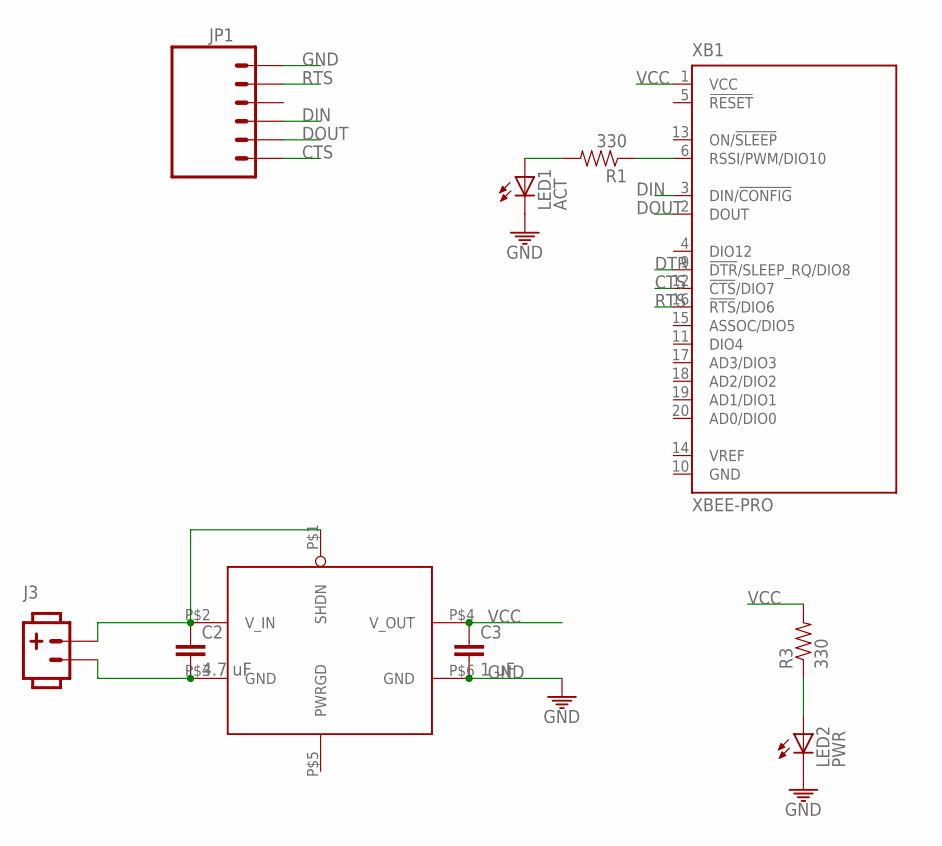
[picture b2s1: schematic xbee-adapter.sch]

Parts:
C2: 4.7 uF; 1206
C3: 1 uF; 1206
J3: POW_CONNECTMALE; SOCKET-MALE-3.96MM-2
JP1: M06LOCK; 1X06_LOCK
LED1: ACT; LED5MM
LED2: PWR; LED5MM
R1, R3: 330; 0805
U$1: MCP1826; SOT223-5
XB1: XBEE-PRO

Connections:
CTS: JP1.6, XB1.12 (!CTS!/DIO7)
DIN: JP1.4, XB1.3 (DIN/!CONFIG)
DOUT: JP1.5, XB1.2 (DOUT)
DTR: XB1.9 (!DTR!/SLEEP_RQ/DIO8)
GND: C2.2, C3.2, J3.P$2 (2), JP1.1, LED1.K (C), LED2.K (C), U$1.P$3 (GND), U$1.P$6 (GND), XB1.10 (GND)
unnamed: LED2.A, R3.1
unnamed: R1.1, XB1.6 (RSSI/PWM/DIO10)
unnamed: LED1.A, R1.2
RTS: JP1.2, XB1.16 (!RTS!/DIO6)
VCC: C3.1, R3.2, U$1.P$4 (V_OUT), XB1.1 (VCC)
VIN: C2.1, J3.P$1 (1), U$1.P$1 (SHDN), U$1.P$2 (V_IN)
